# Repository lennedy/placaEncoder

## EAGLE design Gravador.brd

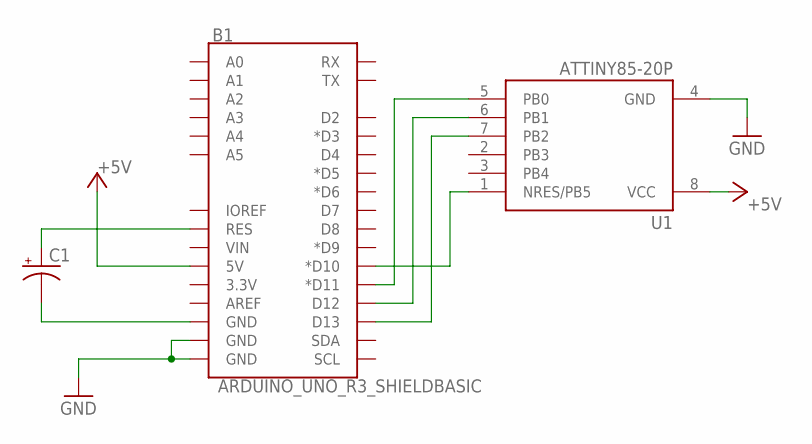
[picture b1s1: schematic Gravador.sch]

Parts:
B1: ARDUINO_UNO_R3_SHIELDBASIC; UNO_R3_SHIELD
C1: CPOL-USE2.5-5; E2,5-5
U1: ATTINY85-20P; PDIP08_300MIL

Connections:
+5V: B1.5V, U1.8 (VCC)
GND: B1.GND@0 (GND), B1.GND@1 (GND), U1.4 (GND)
GND1: B1.GND@2 (GND), C1.-
unnamed: B1.RES, C1.+
unnamed: B1.D13, U1.7 (PB2)
unnamed: B1.D12, U1.6 (PB1)
unnamed: B1.D11 (*D11), U1.5 (PB0)
unnamed: B1.D10 (*D10), U1.1 (NRES/PB5)

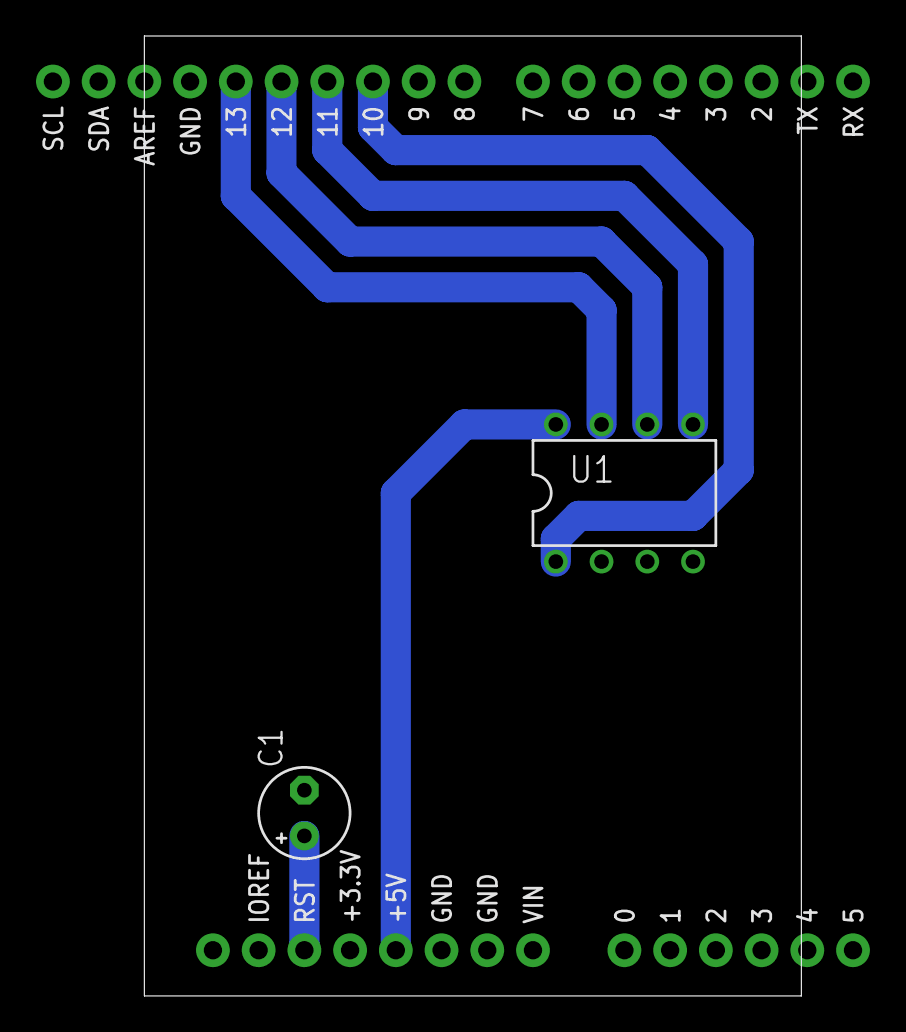
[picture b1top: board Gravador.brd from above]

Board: 2 copper layers, 36.5 x 53.3 mm, 3 parts (0 on the bottom side), 8 nets.

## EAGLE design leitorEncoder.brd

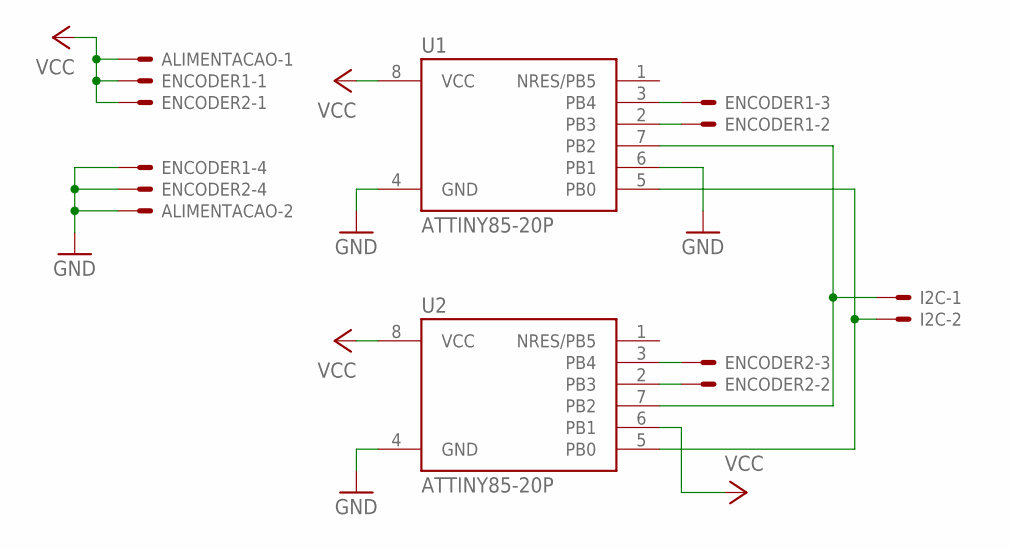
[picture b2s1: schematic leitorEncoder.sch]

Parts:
ALIMENTACAO: CONN_0227-2021; 6410-02
ENCODER1, ENCODER2: CONN_0427-2041; 6410-04
I2C: CONN_0227-2021; 6410-02
U1, U2: ATTINY85-20P; PDIP08_300MIL

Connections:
GND: ALIMENTACAO.2, ENCODER1.4, ENCODER2.4, U1.4 (GND), U1.6 (PB1), U2.4 (GND)
unnamed: I2C.2, U1.5 (PB0), U2.5 (PB0)
unnamed: I2C.1, U1.7 (PB2), U2.7 (PB2)
unnamed: ENCODER2.2, U2.2 (PB3)
unnamed: ENCODER1.3, U1.3 (PB4)
unnamed: ENCODER1.2, U1.2 (PB3)
unnamed: ENCODER2.3, U2.3 (PB4)
VCC: ALIMENTACAO.1, ENCODER1.1, ENCODER2.1, U1.8 (VCC), U2.6 (PB1), U2.8 (VCC)

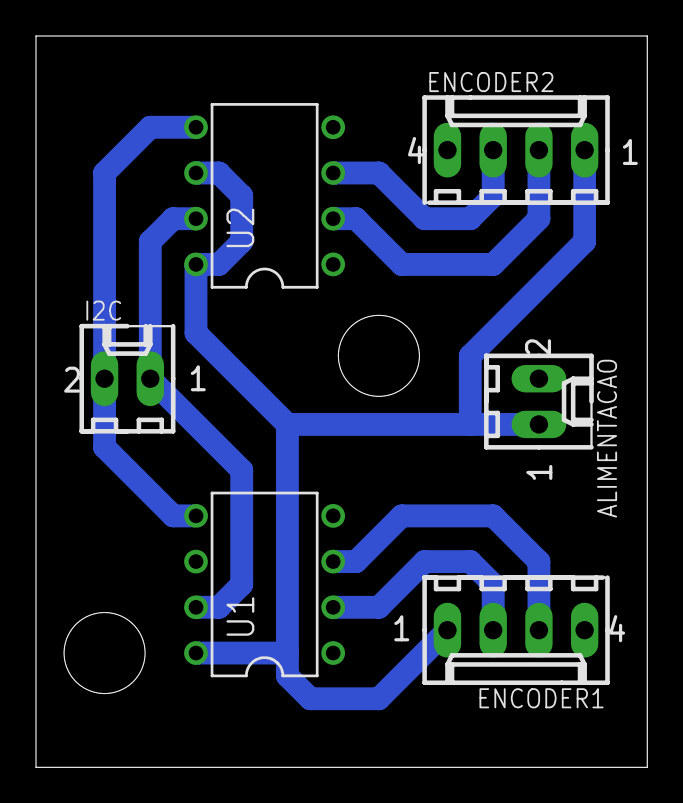
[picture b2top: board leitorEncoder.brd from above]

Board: 2 copper layers, 34.0 x 40.6 mm, 6 parts (0 on the bottom side), 8 nets.

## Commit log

2018-09-25 Criação de placa de para encoders
2018-09-26 Gravador
    Criação de placa para gravar o attiny utilizando o arduino uno
